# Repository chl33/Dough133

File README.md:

# Dough133 (v1.1.0)

Dough133 is a temperature-controlled container for proofing and fermenting sourdough.
It uses a small cooler and a PTC heater with a fan to heat the inside of the cooler.
A PCBA with an ESP32 controls the power supplied to the heater to regulate
 the temperature of the enclosure.

This repository contains:
- KiCAD design for the PCB.
- Source code for the device firmware.
- OpenSCAD design for 3D printed components.

[Instructions for the assembly](https://selectiveappeal.org/posts/dough133-assembly/)
 of the device are in this are at my blog.

Please also see the other entries describing this project:
- [Building a DIY Sourdough Proofer (Dough133)](https://selectiveappeal.org/posts/dough133/),
- [Dough133 Electronics: Designing a Custom ESP32 Controller for Proofing Sourdough](https://selectiveappeal.org/posts/dough133-electronics/), and
- [Dough133 Control: Yeast Welfare through Applied Mathematics](https://selectiveappeal.org/posts/dough133-control/).

Components needed for making this device, along with links and approximate price as of September
 2024:

| Item | Source  | Approximate cost  |
|---|---|---|
| Coleman 16 qt cooler | [Amazon](https://www.amazon.com/gp/product/B09HN13FN4) | $23 |
| PTC Air Heater 12V 100W | [AliExpress](https://www.aliexpress.us/item/3256803451720173.html) | $7 |
| DC 12V 5A Power Supply | [Amazon](https://www.amazon.com/gp/product/B01GEA8PQA)  | $12  |

## KiCAD

The circuit board design is in [KiCAD/](KiCAD/).

These require footprints in [`chl33_library`](https://github.com/chl33/chl33_library.pretty) and symbols in [`chl33_kicad_sym`](https://github.com/chl33/chl33_kicad_sym).

## OpenSCAD

Designs for 3D-printable components are in [scad/](scad/).

The EBox is based on the [ProjectBox](https://github.com/chl33/ProjectBox) OpenSCAD system.

The heater mount secures the heater and temperature/humidity sensor inside the cooler.

The Cooler plug helps avoid heat leaking through the hole through which wires run from the
 heater mount through the wall of the cooler to the EBox.

## Software

The software is based on the [og3](https://github.com/chl33/og3) library and built
 using [PlatformIO](https://platformio.org/).

### Features

*   **Modern Web Interface:** A responsive Svelte-based UI for real-time status monitoring, PID tuning, and system configuration.
*   **PID Temperature Control:** Uses a Proportional-Integral-Derivative controller with feedforward to maintain precise temperature.
*   **Manual Fan Control:** Toggle the enclosure fan manually via the web interface.
*   **Home Assistant & Adafruit IO Integration:** Supports MQTT auto-discovery for seamless integration with Home Assistant as a generic thermostat, as well as SSL/TLS and Adafruit IO broker modes.
*   **Safety Features:** Includes max/min temperature limits, sensor error detection, `WifiWatchdog` recovery, and a software-monitored `200 Hz` heartbeat pulse for the hardware safety circuit (`SN74LVC1G123`) to cut heater power if the main loop or control loop stalls.

### Getting Started

#### Prerequisites

*   [PlatformIO](https://platformio.org/install) (CLI or VSCode extension).
*   [Node.js](https://nodejs.org/) (v22+) and `npm` for building the Svelte web interface.

#### Configuration

The project uses `ini` files for local configuration and secrets. Create `secrets.ini` and `local.ini` based on the provided examples:

1.  **Secrets (`secrets.ini`):**
    Copy `secrets.ini.example` to `secrets.ini` and configure:
    ```ini
    [secrets]
    otaPassword = my_secure_password ; Password for Over-The-Air updates
    ```

2.  **Local Build & Upload Settings (`local.ini`):**
    Copy `local.ini.example` to `local.ini`:
    ```ini
    [platformio]
    default_envs = wifi              ; Use 'usb' for serial flashing or 'wifi' for OTA

    [local]
    uploadPort = 192.168.1.100       ; IP address of the board for OTA uploads
    build_flags =
        '-D LOG_UDP'
        '-D LOG_UDP_ADDRESS=192, 168, 1, 50'
    wifi_upload_flags =
    ```

#### Building and Flashing

1.  Install Svelte frontend dependencies (first time):
    ```bash
    cd svelte && npm ci && cd ..
    ```
2.  Build and upload the firmware (via USB or OTA depending on `default_envs` or `-e`):
    ```bash
    pio run -e usb -t upload   # Flash via USB (/dev/ttyUSB0)
    pio run -e wifi -t upload  # Flash via OTA
    ```
3.  Monitor the serial output to verify startup:
    ```bash
    pio device monitor
    ```

### Usage

#### Physical Interface

*   **Button:** Press the physical button to toggle temperature control ON or OFF.
*   **OLED Screen:** Displays the current state (Off, Running, Cooling), current temperature, and target temperature.

#### Web Interface

Once connected to WiFi, navigate to the device's IP address (displayed on the OLED).
*   **Status Page:** View current temperatures (Enclosure, Room), humidity, and heater status.
*   **Controls:** Enable/Disable the heater.
*   **Configuration:** Set the target temperature, ramp rates, and PID gains.

#### Home Assistant

Ensure your MQTT broker details are configured in the Web UI.
The device will automatically appear in Home Assistant as a climate device
 (Thermostat) if MQTT discovery is enabled.

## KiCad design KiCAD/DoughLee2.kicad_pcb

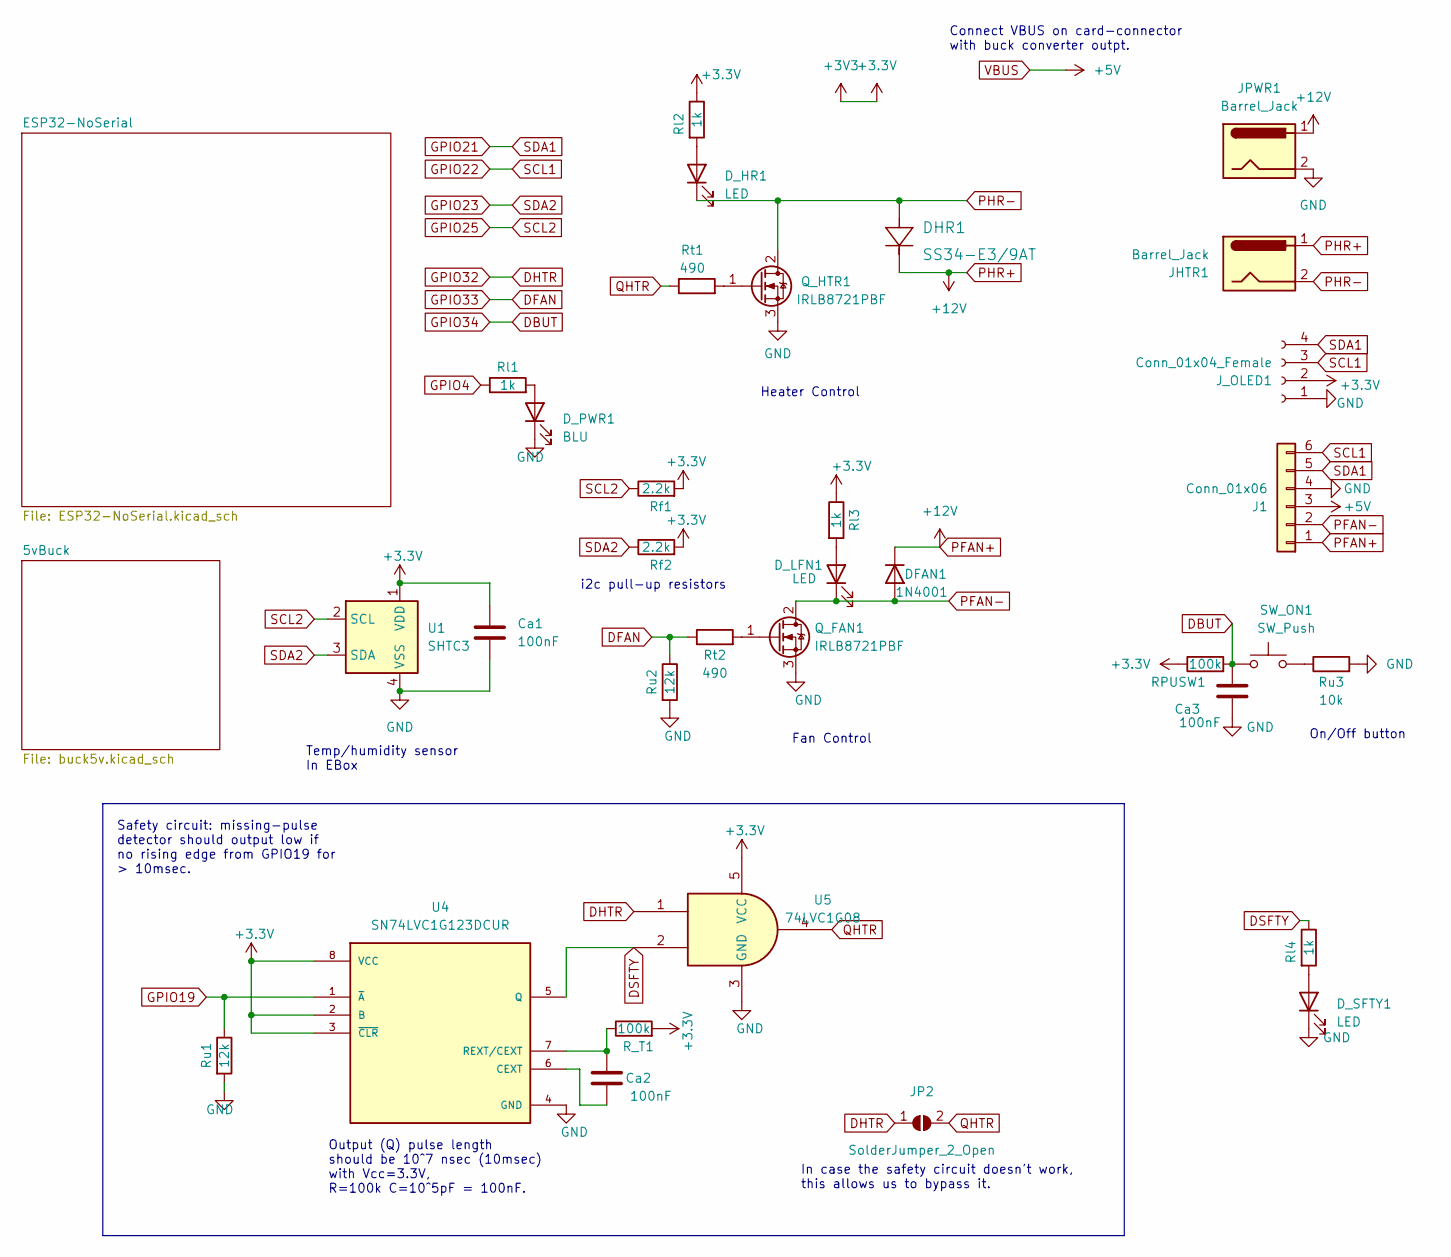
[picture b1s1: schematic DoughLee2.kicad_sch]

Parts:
Ca1, Ca2, Ca3: 100nF; C_0603_1608Metric
DFAN1: 1N4001; D_SMB
DHR1: SS34-E3/9AT; D_SMB
D_HR1: LED; LED_0603_1608Metric
D_LFN1: LED; LED_0603_1608Metric
D_PWR1: BLU; LED_0603_1608Metric
D_SFTY1: LED; LED_0603_1608Metric
J1: Conn_01x06; JST_XH_B6B-XH-A_1x06_P2.50mm_Vertical
JHTR1: Barrel_Jack; BarrelJack_Horizontal
JP2: SolderJumper_2_Open; SolderJumper-2_P1.3mm_Open_Pad1.0x1.5mm
JPWR1: Barrel_Jack; BarrelJack_Horizontal
J_OLED1: Conn_01x04_Female; PinSocket_1x04_P2.54mm_Vertical
Q_FAN1: IRLB8721PBF; TO-220-3_Vertical
Q_HTR1: IRLB8721PBF; TO-220-3_Vertical
RPUSW1: 100k; R_0603_1608Metric
R_T1: 100k; R_0603_1608Metric
Rf1, Rf2: 2.2k; R_0603_1608Metric
Rl1, Rl2, Rl3, Rl4: 1k; R_0603_1608Metric
Rt1, Rt2: 490; R_0603_1608Metric
Ru1, Ru2: 12k; R_0603_1608Metric
Ru3: 10k; R_0603_1608Metric
SW_ON1: SW_Push; SW_PUSH_6mm
U1: SHTC3; Sensirion_DFN-4-1EP_2x2mm_P1mm_EP0.7x1.6mm
U4: SN74LVC1G123DCUR; SOP50P310X90-8N
U5: 74LVC1G08; SOT-23-5

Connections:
+3.3V: Ca1.1, J_OLED1.2, RPUSW1.1, R_T1.2, Rf1.2, Rf2.2, Rl2.1, Rl3.1, U1.1 (VDD), U4.2 (B), U4.3 (~CLR), U4.8 (VCC), U5.5 (VCC); also elsewhere on the board
DBUT: Ca3.1, RPUSW1.2, SW_ON1.1; also elsewhere on the board
DFAN: Rt2.1, Ru2.1; also elsewhere on the board
DHTR: JP2.1 (A), U5.1; also elsewhere on the board
DSFTY: Rl4.1, U4.5 (Q), U5.2
GND: Ca1.2, Ca3.2, D_PWR1.1 (K), D_SFTY1.1 (K), J1.4, JPWR1.2, J_OLED1.1, Q_FAN1.3 (S), Q_HTR1.3 (S), Ru1.2, Ru2.2, Ru3.2, U1.4 (VSS), U4.4 (GND), U5.3 (GND); also elsewhere on the board
GPIO4: Rl1.1; also elsewhere on the board
GPIO19: Ru1.1, U4.1 (~A); also elsewhere on the board
GPIO21: J1.5, J_OLED1.4; also elsewhere on the board
GPIO22: J1.6, J_OLED1.3; also elsewhere on the board
GPIO23: Rf2.1, U1.3 (SDA); also elsewhere on the board
GPIO25: Rf1.1, U1.2 (SCL); also elsewhere on the board
unnamed: D_HR1.2 (A), Rl2.2
unnamed: D_LFN1.2 (A), Rl3.2
unnamed: D_PWR1.2 (A), Rl1.2
unnamed: D_SFTY1.2 (A), Rl4.2
unnamed: Q_FAN1.1 (G), Rt2.2
unnamed: Q_HTR1.1 (G), Rt1.2
unnamed: Ru3.1, SW_ON1.2
unnamed: Ca2.2, U4.6 (CEXT)
unnamed: Ca2.1, R_T1.1, U4.7 (REXT/CEXT)
PFAN+: DFAN1.1 (K), DHR1.1 (ANODE), J1.1, JHTR1.1, JPWR1.1; also elsewhere on the board
PFAN-: DFAN1.2 (A), D_LFN1.1 (K), J1.2, Q_FAN1.2 (D)
PHR-: DHR1.2 (CATHODE), D_HR1.1 (K), JHTR1.2, Q_HTR1.2 (D)
QHTR: JP2.2 (B), Rt1.1, U5.4
VBUS: J1.3; also elsewhere on the board

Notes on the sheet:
On/Off button
Heater Control
In case the safety circuit doesn't work, this allows us to bypass it.
Connect VBUS on card-connector with buck converter outpt.
i2c pull-up resistors
Fan Control
Safety circuit: missing-pulse detector should output low if no rising edge from GPIO19 for > 10msec.
Output (Q) pulse length should be 10^7 nsec (10msec) with Vcc=3.3V, R=100k C=10^5pF = 100nF.
Temp/humidity sensor In EBox

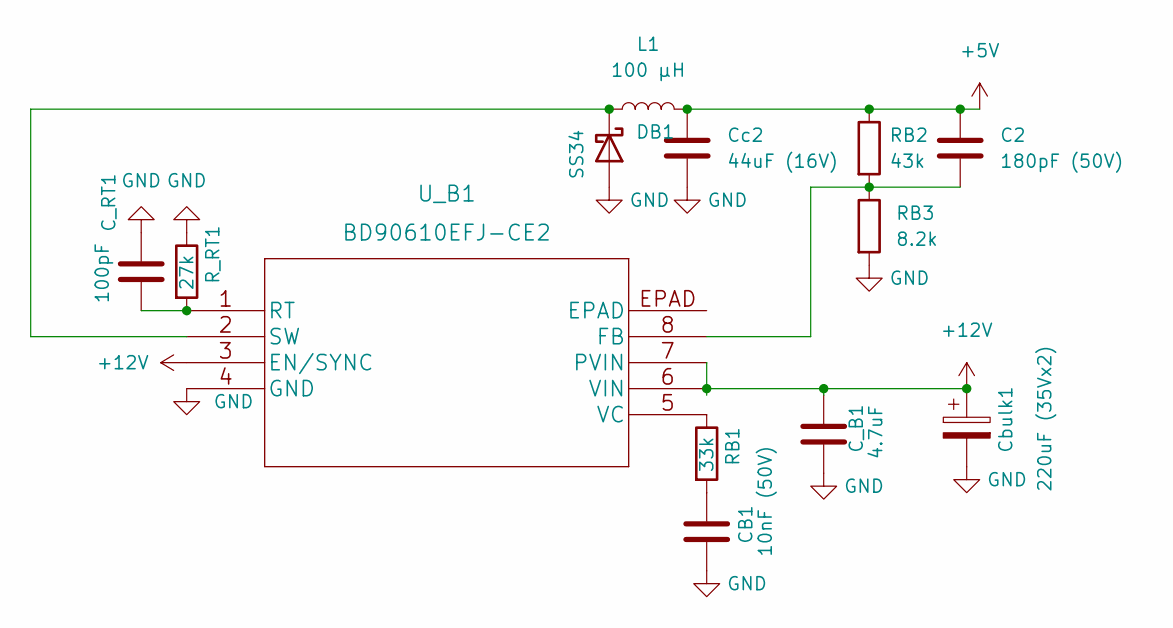
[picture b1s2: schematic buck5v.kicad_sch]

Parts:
C2: 180pF (50V); C_0603_1608Metric
CB1: 10nF (50V); C_0805_2012Metric_Pad1.18x1.45mm_HandSolder
C_B1: 4.7uF; C_0805_2012Metric_Pad1.18x1.45mm_HandSolder
C_RT1: 100pF; C_0603_1608Metric_Pad1.08x0.95mm_HandSolder
Cbulk1: 220uF (35Vx2); CP_Radial_D6.3mm_P2.50mm
Cc2: 44uF (16V); C_0603_1608Metric
DB1: SS34; D_SMA
L1: 100 μH; CD54
RB1: 33k; R_0603_1608Metric
RB2: 43k; R_0603_1608Metric
RB3: 8.2k; R_0603_1608Metric
R_RT1: 27k; R_0603_1608Metric
U_B1: BD90610EFJ-CE2; HTSOP-J8_ROM

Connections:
GND: CB1.2, C_B1.2, C_RT1.1, Cbulk1.2, Cc2.2, DB1.2 (A), RB3.2, R_RT1.1, U_B1.4 (GND); also elsewhere on the board
unnamed: CB1.1, RB1.2
unnamed: DB1.1 (K), L1.1, U_B1.2 (SW)
unnamed: C2.2, RB2.2, RB3.1, U_B1.8 (FB)
unnamed: C_RT1.2, R_RT1.2, U_B1.1 (RT)
unnamed: RB1.1, U_B1.5 (VC)
PFAN+: C_B1.1, Cbulk1.1, U_B1.3 (EN/SYNC), U_B1.6 (VIN), U_B1.7 (PVIN); also elsewhere on the board
VBUS: C2.1, Cc2.1, L1.2, RB2.1; also elsewhere on the board

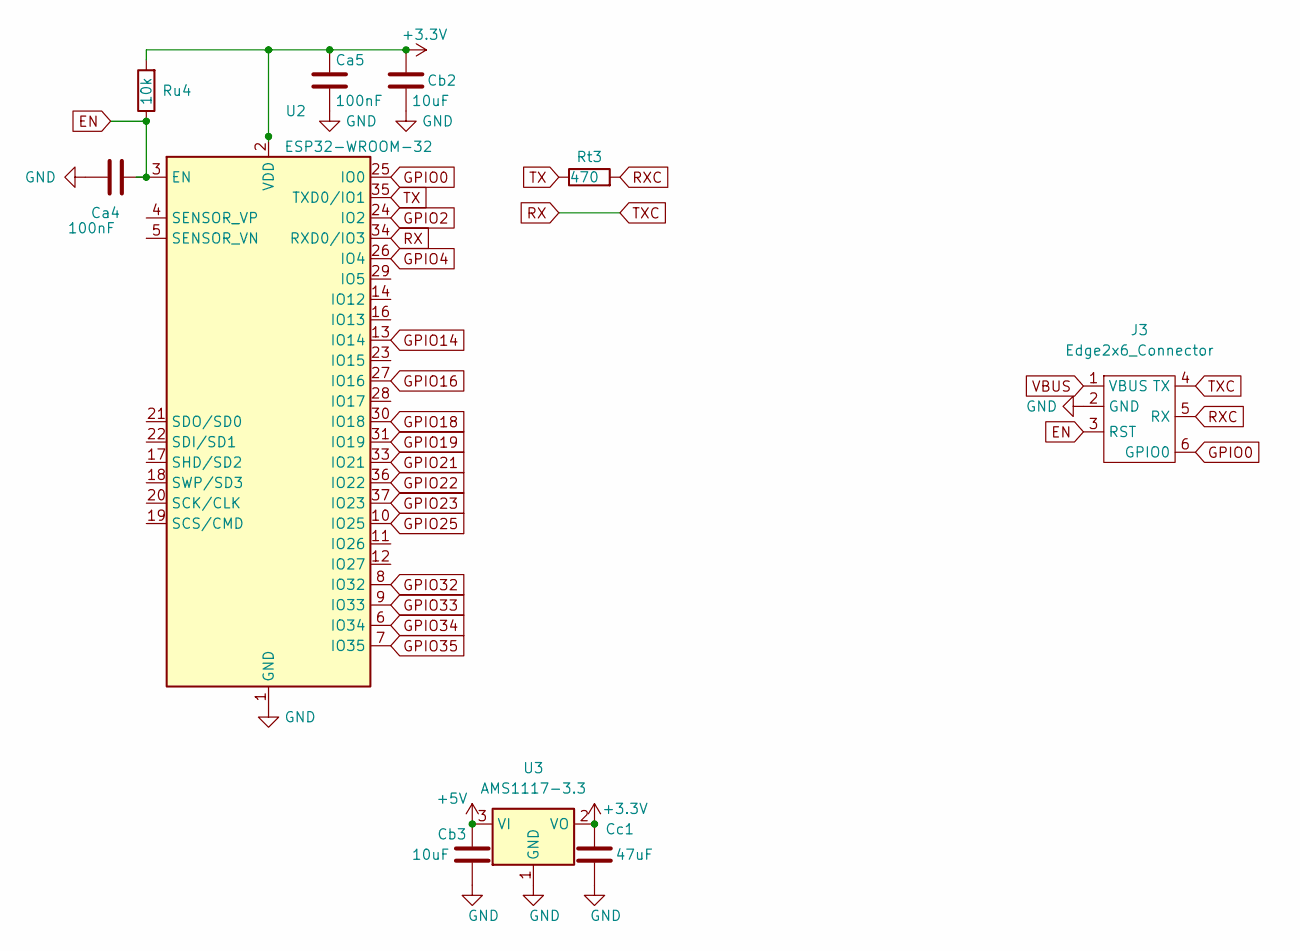
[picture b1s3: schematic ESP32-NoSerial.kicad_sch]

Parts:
Ca4, Ca5: 100nF; C_0603_1608Metric
Cb2, Cb3: 10uF; C_0805_2012Metric_Pad1.18x1.45mm_HandSolder
Cc1: 47uF; C_0805_2012Metric_Pad1.18x1.45mm_HandSolder
J3: Edge2x6_Connector; EdgeConnector_2x3
Rt3: 470; R_0603_1608Metric
Ru4: 10k; R_0603_1608Metric
U2: ESP32-WROOM-32
U3: AMS1117-3.3; SOT-223-3_TabPin2

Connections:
+3.3V: Ca5.1, Cb2.1, Cc1.1, Ru4.2, U2.2 (VDD), U3.2 (VO); also elsewhere on the board
DBUT: U2.6 (IO34); also elsewhere on the board
DFAN: U2.9 (IO33); also elsewhere on the board
DHTR: U2.8 (IO32); also elsewhere on the board
EN: Ca4.2, J3.3 (RST), Ru4.1, U2.3 (EN)
GND: Ca4.1, Ca5.2, Cb2.2, Cb3.2, Cc1.2, J3.2 (GND), U2.1 (GND), U2.15 (GND), U2.38 (GND), U2.39 (GND), U3.1 (GND); also elsewhere on the board
GPIO0: J3.6 (GPIO0), U2.25 (IO0)
GPIO2: U2.24 (IO2)
GPIO4: U2.26 (IO4); also elsewhere on the board
GPIO14: U2.13 (IO14)
GPIO16: U2.27 (IO16); also elsewhere on the board
GPIO18: U2.30 (IO18)
GPIO19: U2.31 (IO19); also elsewhere on the board
GPIO21: U2.33 (IO21); also elsewhere on the board
GPIO22: U2.36 (IO22); also elsewhere on the board
GPIO23: U2.37 (IO23); also elsewhere on the board
GPIO25: U2.10 (IO25); also elsewhere on the board
GPIO35: U2.7 (IO35)
RX: J3.4 (TX), U2.34 (RXD0/IO3)
RXC: J3.5 (RX), Rt3.2
TX: Rt3.1, U2.35 (TXD0/IO1)
VBUS: Cb3.1, J3.1 (VBUS), U3.3 (VI); also elsewhere on the board

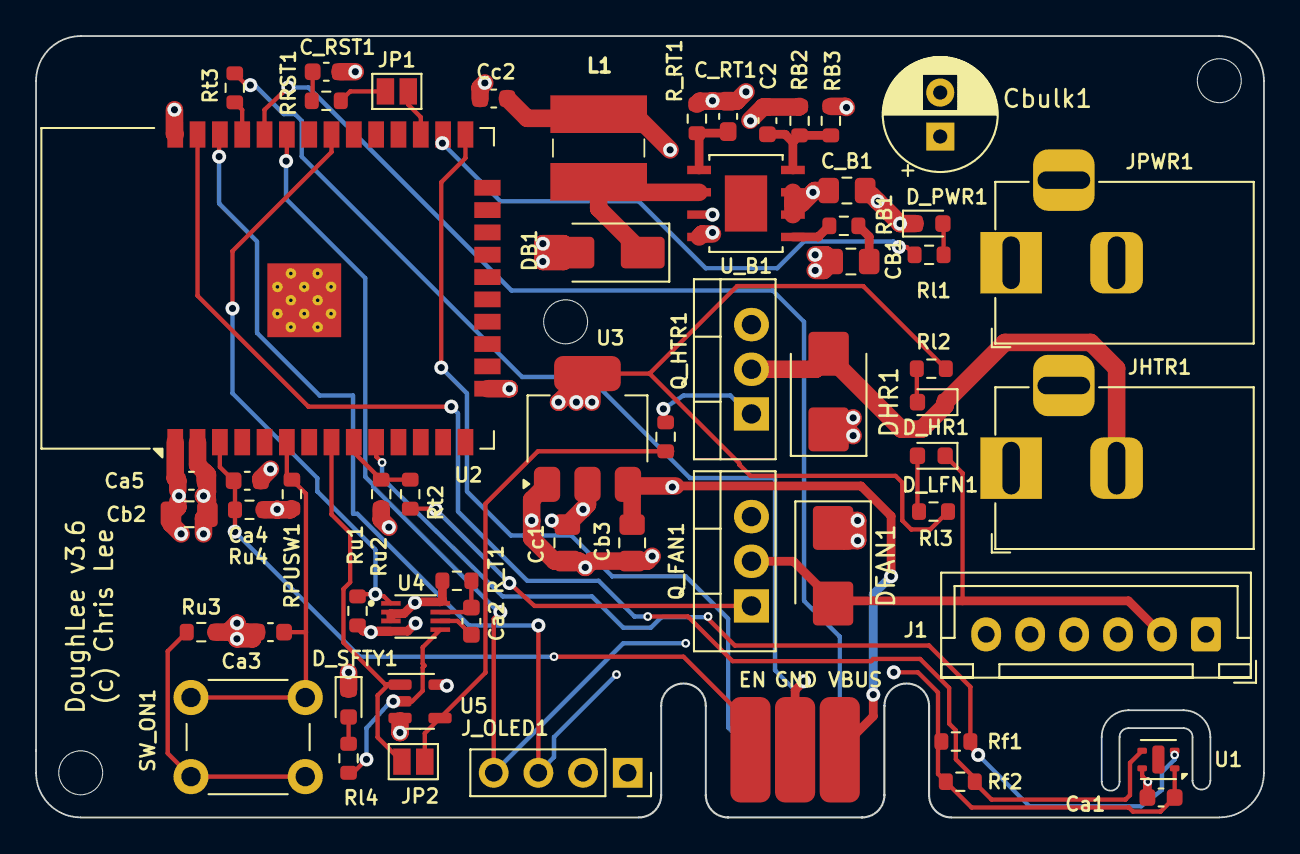
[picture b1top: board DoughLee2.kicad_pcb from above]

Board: 4 copper layers, 69.8 x 44.4 mm, 59 parts (0 on the bottom side), 39 nets.

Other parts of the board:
C_RST1: 100nF; C_0603_1608Metric
JP1: SolderJumper_2_Open; SolderJumper-2_P1.3mm_Open_Pad1.0x1.5mm
RRST1: 470; R_0603_1608Metric

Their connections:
GND: C_RST1.2; also elsewhere on the board
GPIO16: JP1.2 (B); also elsewhere on the board
unnamed: JP1.1 (A), RRST1.2
RST: C_RST1.1, RRST1.1

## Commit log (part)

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2024-09-28 Initial import
2024-09-28 Initial import (#1)
2024-09-29 image paths
2024-09-29 Chl33/readme (#2)
2024-09-29 add links and prices of stuff to buy
2024-09-29 add links and prices of stuff to buy (#3)
2024-10-13 Updated KiCAD design
    - Fix library locations
    - Update some footprints and symbols
    - Added missing +3.3V to SHTC3
    - Removed jumper from edge-connector power and replaced with wire
2024-10-13 Tried to fix SHTC3 Wire1 initialization
    This is baed on experimentation with a breadboard and a sensor module.
2024-10-13 README: point to kicad repositorie
2024-10-13 shtc3 fixes (#4)
    Updates to KiCAD design:
    - Fix library locations
    - Update some footprints and symbols
    - Added missing +3.3V to SHTC3
    - Removed jumper from edge-connector power and replaced with wire
    main.cpp: Tried to fix i2c initialization for room SHTC3 sensor in ebox.
2024-10-19 Update dependencies
2024-10-19 Update dependencies (#5)
2024-10-19 Add state for performing system identification.
    - Turn on fan and heater full-on for 60 seconds.
    - Turn off heater and keep fan on for another 60 seconds.
2024-10-24 update workflows
2024-10-24 update license header
2024-10-24 tweak workflow
2024-10-24 update workflows (#7)
    * update workflows
    * update dependencies
    * update license header
2025-08-24 upgrade og3 to version 0.3.90
2025-08-24 github action platformio needs intelhex installed
2025-10-26 version update again
2026-02-01 Ramp temperature setpoint smoothly (gemini). Untested.
2026-02-01 dependency updates
2026-02-01 Set target d(temp)/dt, do more checking of temperature value.
2026-02-02 Base commanded d_target to what way we want temp to move.
2026-02-02 fan_mode is manual override for can control, mqtt for fan relay state
2026-02-02 add uploadHostPort in example secrets
2026-02-02 Version 0.9.95: input shaping (#8)
    - Update og3 to 0.4.3.
    - Use input shaping to avoid overshooting temperature setpoint.
    - Fan control now overrides fan relay when high.
    - Report actual fan relay state.
2026-02-02 readme improvements
2026-02-02 updated blog post titles
2026-02-02 readme improvements (#9)
2026-02-08 Start sending data via MQTT when first turned on.
    Before, it only sent data after control started.
2026-02-08 Added a test state. It sends 'cmd_test' as constant PWM command.
2026-02-08 version -> 0.9.96
2026-02-11 version 0.9.96 (#10)
    * Start sending data via MQTT when first turned on.
    Before, it only sent data after control started.
    * Added a test state. It sends 'cmd_test' as constant PWM command.
    * version -> 0.9.96
2026-02-12 Allow 70deg max in enclosure, show pwm when cmd starts
    Also disable debug prints.
2026-02-12 print SHTC3 room reading failure warning only once
2026-02-12 version 0 9 96 (#12)
    * Allow 70deg max in enclosure, show pwm when cmd starts
    * Disable debug prints.
    * print SHTC3 room reading failure warning only once
2026-02-12 Analysis of PWM command -> power.
    Gemini-generated
2026-02-12 ruff changes for gui.py
2026-02-12 add ruff to github actions
2026-02-12 update ruff linting
2026-02-12 fix platform.io
2026-02-12 analyze_pwm.py: coding tweak
2026-02-12 required license header on python
2026-02-12 analyze_pwm.py: ruff fixes
2026-02-12 update copyright, add copyright header to python
2026-02-12 PWM_to_Watts/setup.py -> run.sh
2026-02-12 pre-commit: add ruff
2026-02-12 test commit
2026-02-12 ruff config
2026-02-12 analyze_pwm.py: remove commented-out code
2026-02-12 add data point for PWM=0.5
2026-02-12 improved script for running pwm analysis
2026-02-12 pwm -> Watt analysis (#11)
    - Script or for fitting pwm -> Watts and generating a plotly plot for the blog.
    - Added ruff support for the Python: pre-command and github-actions.
2026-02-13 cooling analysis (gemini)
2026-02-14 version -> 0.9.97: add optional timeout for test-command
    E.g., this can be used to deliver a (near) impulse.
    Also, upgrade og3 version to fix PID error.
2026-02-14 version -> 0.9.97: add optional timeout for test-command (#13)
    Add optional timeout for test-command E.g., this can be used to deliver a (near) impulse.
    Upgrade og3 version to fix PID error.
    Add cooler cool-down analysis by Gemini.
    Update README
2026-03-25 updated for og3 0.6.0 (gemini)
2026-03-29 added dependabot (gemini)
2026-03-29 Svelte interface built by Gemini(!)
2026-03-29 build fixes (gemini)
2026-03-29 updates from gemini -- to match update PID names
2026-03-29 Clamping 0-1 should not be configured by web interface.
2026-03-29 Fix partition, buttons for fan mode, test mode
2026-03-30 fixed value editing on web page (gemini)
2026-03-30 better organize local build
2026-03-30 update example local config
2026-03-30 update deps to published versions
2026-03-30 version -> 1.0.0
2026-03-30 updates for v1.0.0
2026-03-30 update platformio workflow
2026-03-30 Version -> 1.0.0 (#14)
    ### Added
    - New responsive Svelte web interface for status monitoring and configuration.
    - JSON API for full device control and status reporting.
    - Standardized `camelCase` naming for all API keys and internal variables.
    - Manual fan control via web UI.
    - Integrated "Run Test" command button in configuration page.
2026-03-30 Bump actions/setup-node from 4 to 6
    Bumps [actions/setup-node](https://github.com/actions/setup-node) from 4 to 6.
    - [Release notes](https://github.com/actions/setup-node/releases)
    - [Commits](https://github.com/actions/setup-node/compare/v4...v6)
    ---
    updated-dependencies:
    - dependency-name: actions/setup-node
2026-03-30 Bump actions/checkout from 4 to 6
    Bumps [actions/checkout](https://github.com/actions/checkout) from 4 to 6.
    - [Release notes](https://github.com/actions/checkout/releases)
    - [Changelog](https://github.com/actions/checkout/blob/main/CHANGELOG.md)
    - [Commits](https://github.com/actions/checkout/compare/v4...v6)
    ---
    updated-dependencies:
2026-03-30 Bump actions/setup-python from 5 to 6
    Bumps [actions/setup-python](https://github.com/actions/setup-python) from 5 to 6.
    - [Release notes](https://github.com/actions/setup-python/releases)
    - [Commits](https://github.com/actions/setup-python/compare/v5...v6)
    ---
    updated-dependencies:
    - dependency-name: actions/setup-python
2026-03-30 Bump actions/setup-python from 5 to 6 (#18)
    Bumps [actions/setup-python](https://github.com/actions/setup-python) from 5 to 6.
    - [Release notes](https://github.com/actions/setup-python/releases)
    - [Commits](https://github.com/actions/setup-python/compare/v5...v6)
    ---
    updated-dependencies:
    - dependency-name: actions/setup-python
2026-03-30 Bump actions/setup-node from 4 to 6 (#15)
    Bumps [actions/setup-node](https://github.com/actions/setup-node) from 4 to 6.
    - [Release notes](https://github.com/actions/setup-node/releases)
    - [Commits](https://github.com/actions/setup-node/compare/v4...v6)
    ---
    updated-dependencies:
    - dependency-name: actions/setup-node
2026-03-30 Bump actions/checkout from 4 to 6 (#17)
    Bumps [actions/checkout](https://github.com/actions/checkout) from 4 to 6.
    - [Release notes](https://github.com/actions/checkout/releases)
    - [Changelog](https://github.com/actions/checkout/blob/main/CHANGELOG.md)
    - [Commits](https://github.com/actions/checkout/compare/v4...v6)
    ---
    updated-dependencies:
2026-03-30 Bump actions/cache from 4 to 5
    Bumps [actions/cache](https://github.com/actions/cache) from 4 to 5.
    - [Release notes](https://github.com/actions/cache/releases)
    - [Changelog](https://github.com/actions/cache/blob/main/RELEASES.md)
    - [Commits](https://github.com/actions/cache/compare/v4...v5)
    ---
    updated-dependencies:
2026-03-30 Bump actions/cache from 4 to 5 (#16)
    Bumps [actions/cache](https://github.com/actions/cache) from 4 to 5.
    - [Release notes](https://github.com/actions/cache/releases)
    - [Changelog](https://github.com/actions/cache/blob/main/RELEASES.md)
    - [Commits](https://github.com/actions/cache/compare/v4...v5)
    ---
    updated-dependencies:
2026-06-19 Bump actions/checkout from 6 to 7
    Bumps [actions/checkout](https://github.com/actions/checkout) from 6 to 7.
    - [Release notes](https://github.com/actions/checkout/releases)
    - [Changelog](https://github.com/actions/checkout/blob/main/CHANGELOG.md)
    - [Commits](https://github.com/actions/checkout/compare/v6...v7)
    ---
    updated-dependencies:
2026-06-19 Bump actions/checkout from 6 to 7 (#19)
    Bumps [actions/checkout](https://github.com/actions/checkout) from 6 to 7.
    - [Release notes](https://github.com/actions/checkout/releases)
    - [Changelog](https://github.com/actions/checkout/blob/main/CHANGELOG.md)
    - [Commits](https://github.com/actions/checkout/compare/v6...v7)
    ---
    updated-dependencies:
2026-06-24 Bump actions/cache from 5 to 6
    Bumps [actions/cache](https://github.com/actions/cache) from 5 to 6.
    - [Release notes](https://github.com/actions/cache/releases)
    - [Changelog](https://github.com/actions/cache/blob/main/RELEASES.md)
    - [Commits](https://github.com/actions/cache/compare/v5...v6)
    ---
    updated-dependencies:
